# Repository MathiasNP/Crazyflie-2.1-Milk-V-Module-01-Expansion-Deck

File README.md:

# Crazyflie 2.1 Milk-V Duo Module 01 Expansion Deck
This project designs a PCB expansion deck for Bitcraze Crazyflie 2.1 including a dual-core GHz CPU with additional interfaces for communication

---
## CAD program
- **KiCad 9.0** 

## Key components
- **Milk-V Duo Module 01** 
- **SD card connector:** 32GB minimum
- **USB connector pads** 
- **Expansion connectors to Crazyflie** 
- **DC-DC converter for 3.3V**

### For testing
- **Crazyflie 2.1** with Crazyradio USB Dongle
- **Linux computer** 
	- With Docker installed
	- Preferably Linux Mint or Ubuntu
	- Minimum 4GB RAM, 8GB recommended
- **Jumper cables:** For Crazyflie-to-MilkV connection

### Desclaimer
SD/MMC flashing is not possible due to connection problems to the Duo Module. Surmised to be due to the usage of an EMI-Filter with too high series resistance
Recommended to either use the schematic design from the original EVB schematics and/or remove the EMI-Filter

---
## File Reference
- **`BT-MV Duo 01 Deck/`**: Project root folder.

- **`BT-MV Duo 01 Deck.kicad_pcb`**: KiCad PCB layout file.  
- **`BT-MV Duo 01 Deck.kicad_prl`**: KiCad project local settings file.  
- **`BT-MV Duo 01 Deck.kicad_pro`**: KiCad project file.  

- **`MV Duo 01 Deck Schematics/`**: Hierarchical schematics for the deck design.  
  - **`BT-MV Duo 01 Deck.kicad_sch`**: Top-level schematic.  
  - **`BT-Power_CFexp.kicad_sch`**: Power management and Crazyflie expansion interface.  
  - **`BT-SDcard.kicad_sch`**: microSD (SD/MMC) interface.  
  - **`BT-USB_UART.kicad_sch`**: USB interface and UART debug port.  
  - **`BT-CameraOV.kicad_sch`**: Camera connector and related signals.  
  - **`BT-MV_DM01.kicad_sch`**: Milk-V Duo Module 01 integration (pins, power, straps).  
  - **`BT-Others.kicad_sch`**: Miscellaneous signals and support circuits.  

- **`BT-MVD01 libraries/`**: Custom KiCad libraries used by the project.  
  - **`Symbols and Footprints/`**: Symbol/footprint library folder.  
  - **`3D Models/`**: 3D models for custom footprints.  

- **`BT-Milk V Duo S.pretty/`**: KiCad footprint library (`.pretty`).  
- **`BT-MV Duo 01 Deck.csv`**: BOM / component list.  
- **`BT-MV Duo 01 Deck.kicad_dru`**: KiCad custom design rules.  

- **`Related Work/`**: Reference material from related designs.  
  - **`CF Proto Exp/`**: Crazyflie expansion/deck project and documentation.  
  - **`Milk Module schematics/`**: Schematics of the Milk-V module and EVB.  
  - **`Camera OV5674/`**: Reference material for the OV5674 camera.

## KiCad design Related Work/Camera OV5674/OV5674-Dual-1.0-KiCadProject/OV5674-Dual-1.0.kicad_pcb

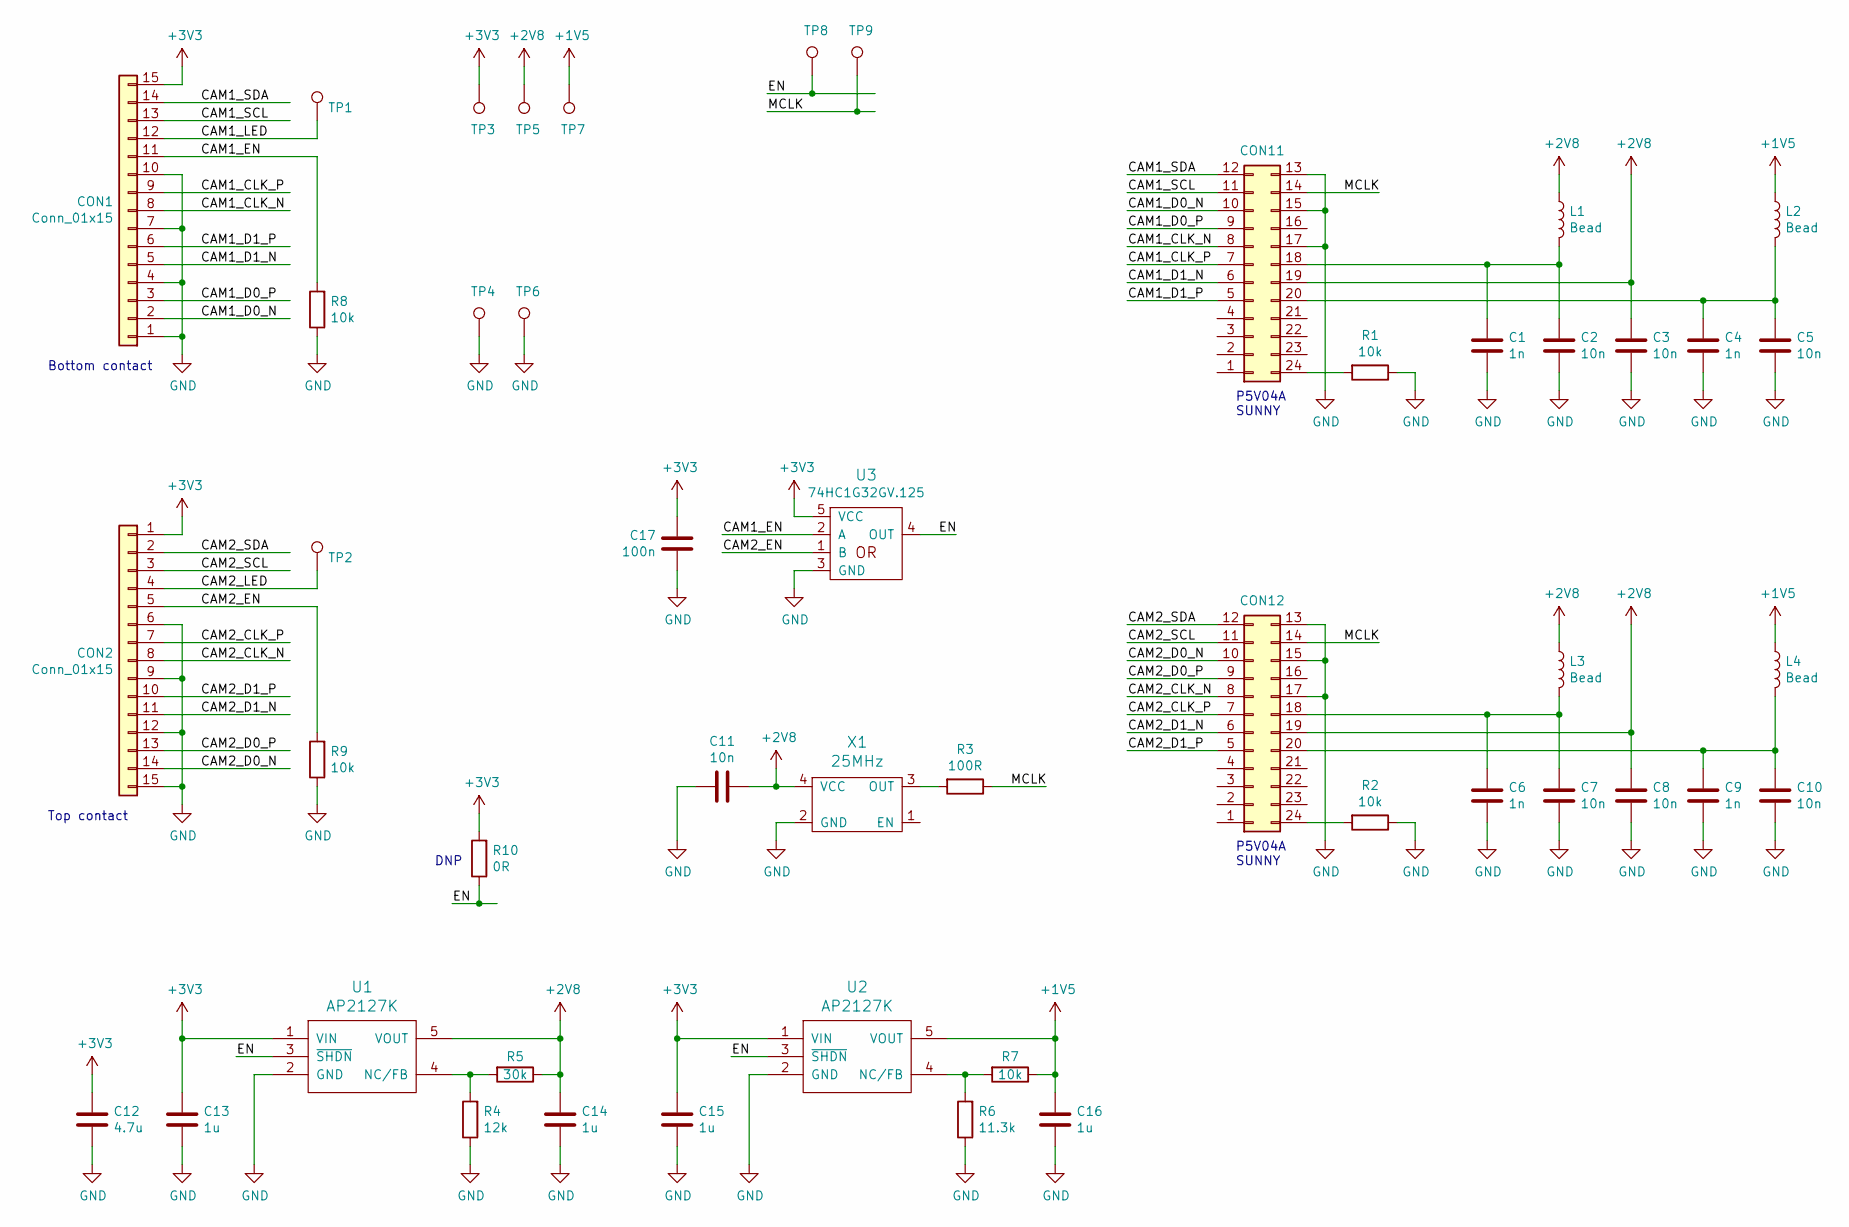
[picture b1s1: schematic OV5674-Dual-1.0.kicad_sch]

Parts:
C1, C4, C6, C9: 1n; C_0603_1608Metric
C2, C3, C5, C7, C8, C10, C11: 10n; C_0603_1608Metric
C12: 4.7u; C_0805_2012Metric
C13, C14, C15, C16: 1u; C_0603_1608Metric
C17: 100n; C_0603_1608Metric
CON1, CON2: Conn_01x15; TE_1-84952-5_1x15-1MP_P1.0mm_Horizontal
CON11, CON12: Conn_02x12_Counter_Clockwise; DF30FC-24DP-0.4V
L1, L2, L3, L4: Bead; L_0805_2012Metric
R1, R2, R7, R8, R9: 10k; R_0603_1608Metric
R3: 100R; R_0603_1608Metric
R4: 12k; R_0603_1608Metric
R5: 30k; R_0603_1608Metric
R6: 11.3k; R_0603_1608Metric
R10: 0R; R_0603_1608Metric
TP1, TP2, TP3, TP4: TestPoint; TestPoint_Pad_D1.5mm
TP5, TP6, TP7, TP8, TP9: TestPoint; TestPoint_Pad_D1.0mm
U1, U2: AP2127K; SOT-23-5
U3: 74xx1G32; SC-74A
X1: 25MHz; CFPS-39

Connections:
+1V5: C16.1, L2.1, L4.1, R7.1, TP7.1, U2.5 (VOUT)
+2V8: C3.1, C8.1, C11.1, C14.1, CON11.19, CON12.19, L1.1, L3.1, R5.1, TP5.1, U1.5 (VOUT), X1.4 (VCC)
+3V3: C12.1, C13.1, C15.1, C17.1, CON1.15, CON2.1, R10.2, TP3.1, U1.1 (VIN), U2.1 (VIN), U3.5 (VCC)
/CAM1_CLK_N: CON1.8, CON11.8
/CAM1_CLK_P: CON1.9, CON11.7
/CAM1_D0_N: CON1.2, CON11.10
/CAM1_D0_P: CON1.3, CON11.9
/CAM1_D1_N: CON1.5, CON11.6
/CAM1_D1_P: CON1.6, CON11.5
/CAM1_EN: CON1.11, R8.2, U3.2 (A)
/CAM1_LED: CON1.12, TP1.1
/CAM1_SCL: CON1.13, CON11.11
/CAM1_SDA: CON1.14, CON11.12
/CAM2_CLK_N: CON2.8, CON12.8
/CAM2_CLK_P: CON2.7, CON12.7
/CAM2_D0_N: CON2.14, CON12.10
/CAM2_D0_P: CON2.13, CON12.9
/CAM2_D1_N: CON2.11, CON12.6
/CAM2_D1_P: CON2.10, CON12.5
/CAM2_EN: CON2.5, R9.2, U3.1 (B)
/CAM2_LED: CON2.4, TP2.1
/CAM2_SCL: CON2.3, CON12.11
/CAM2_SDA: CON2.2, CON12.12
/EN: R10.1, TP8.1, U1.3 (~SHDN), U2.3 (~SHDN), U3.4 (OUT)
/MCLK: CON11.14, CON12.14, R3.1, TP9.1
GND: C1.2, C2.2, C3.2, C4.2, C5.2, C6.2, C7.2, C8.2, C9.2, C10.2, C11.2, C12.2, C13.2, C14.2, C15.2, C16.2, C17.2, CON1.1, CON1.4, CON1.7, CON1.10, CON2.6, CON2.9, CON2.12, CON2.15, CON11.13, CON11.15, CON11.17, CON12.13, CON12.15, CON12.17, R1.1, R2.1, R4.1, R6.1, R8.1, R9.1, TP4.1, TP6.1, U1.2 (GND), U2.2 (GND), U3.3 (GND), X1.2 (GND)
unnamed: C1.1, C2.1, CON11.18, L1.2
unnamed: C4.1, C5.1, CON11.20, L2.2
unnamed: C6.1, C7.1, CON12.18, L3.2
unnamed: C9.1, C10.1, CON12.20, L4.2
unnamed: CON11.24, R1.2
unnamed: CON12.24, R2.2
unnamed: R3.2, X1.3 (OUT)
unnamed: R4.2, R5.2, U1.4 (NC/FB)
unnamed: R6.2, R7.2, U2.4 (NC/FB)

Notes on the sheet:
Bottom contact
DNP
P5V04A SUNNY
Top contact

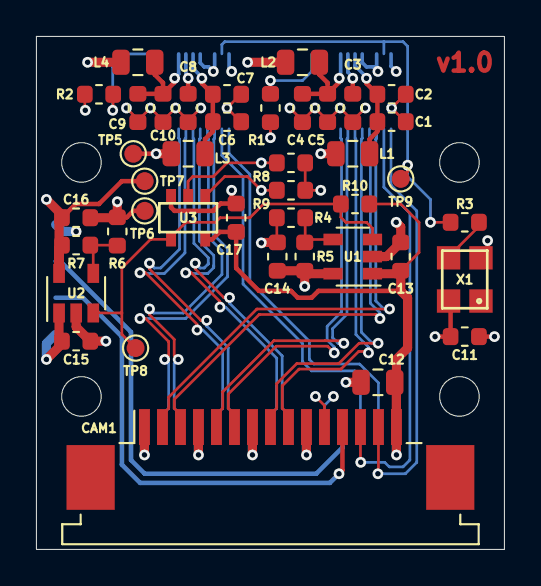
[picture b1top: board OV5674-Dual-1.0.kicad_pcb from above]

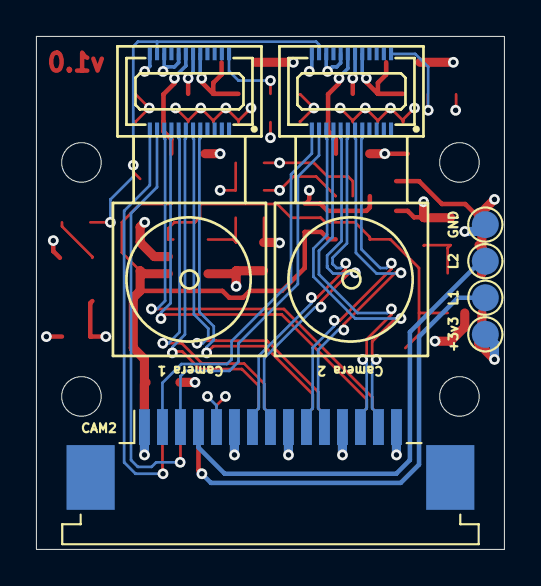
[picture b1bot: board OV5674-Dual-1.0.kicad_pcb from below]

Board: 4 copper layers, 26.0 x 28.5 mm, 48 parts (7 on the bottom side), 35 nets.

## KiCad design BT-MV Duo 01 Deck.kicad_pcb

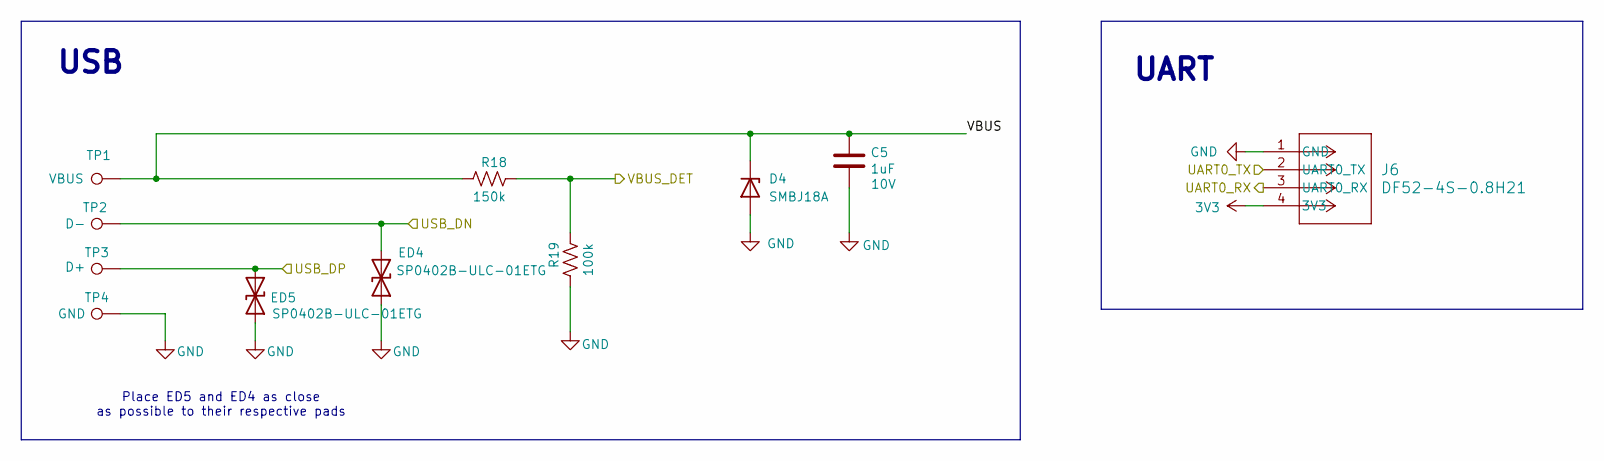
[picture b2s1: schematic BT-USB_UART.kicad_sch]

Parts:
C5: 1uF; C_0603_1608Metric
D4: SMBJ18A; D_SOD-123F
ED4, ED5: SP0402B-ULC-01ETG; D_0402_1005Metric
J6: DF52-4S-0.8H21; CONN4X1_DF52-4S-0.8H21_HIR
R18: 150k; R_0201_0603Metric_Pad0.64x0.40mm_HandSolder
R19: 100k; R_0201_0603Metric_Pad0.64x0.40mm_HandSolder
TP1: VBUS; TestPoint_Pad_D1.0mm
TP2: D-; TestPoint_Pad_D1.0mm
TP3: D+; TestPoint_Pad_D1.0mm
TP4: GND; TestPoint_Pad_D1.0mm

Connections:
3V3: J6.4 (3V3); also elsewhere on the board
/CF Proto EXP/VBUS: C5.1, D4.1 (K), R18.2, TP1.1; also elsewhere on the board
/Milk Module/UART0_RX: J6.3 (UART0_RX); also elsewhere on the board
/Milk Module/UART0_TX: J6.2 (UART0_TX); also elsewhere on the board
/Milk Module/USB_DN: ED4.2 (A2), TP2.1; also elsewhere on the board
/Milk Module/USB_DP: ED5.2 (A2), TP3.1; also elsewhere on the board
/Milk Module/VBUS_DET: R18.1, R19.1; also elsewhere on the board
GND: C5.2, D4.2 (A), ED4.1 (A1), ED5.1 (A1), J6.1 (GND), R19.2, TP4.1; also elsewhere on the board

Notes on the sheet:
UART
USB
Place ED5 and ED4 as close as possible to their respective pads

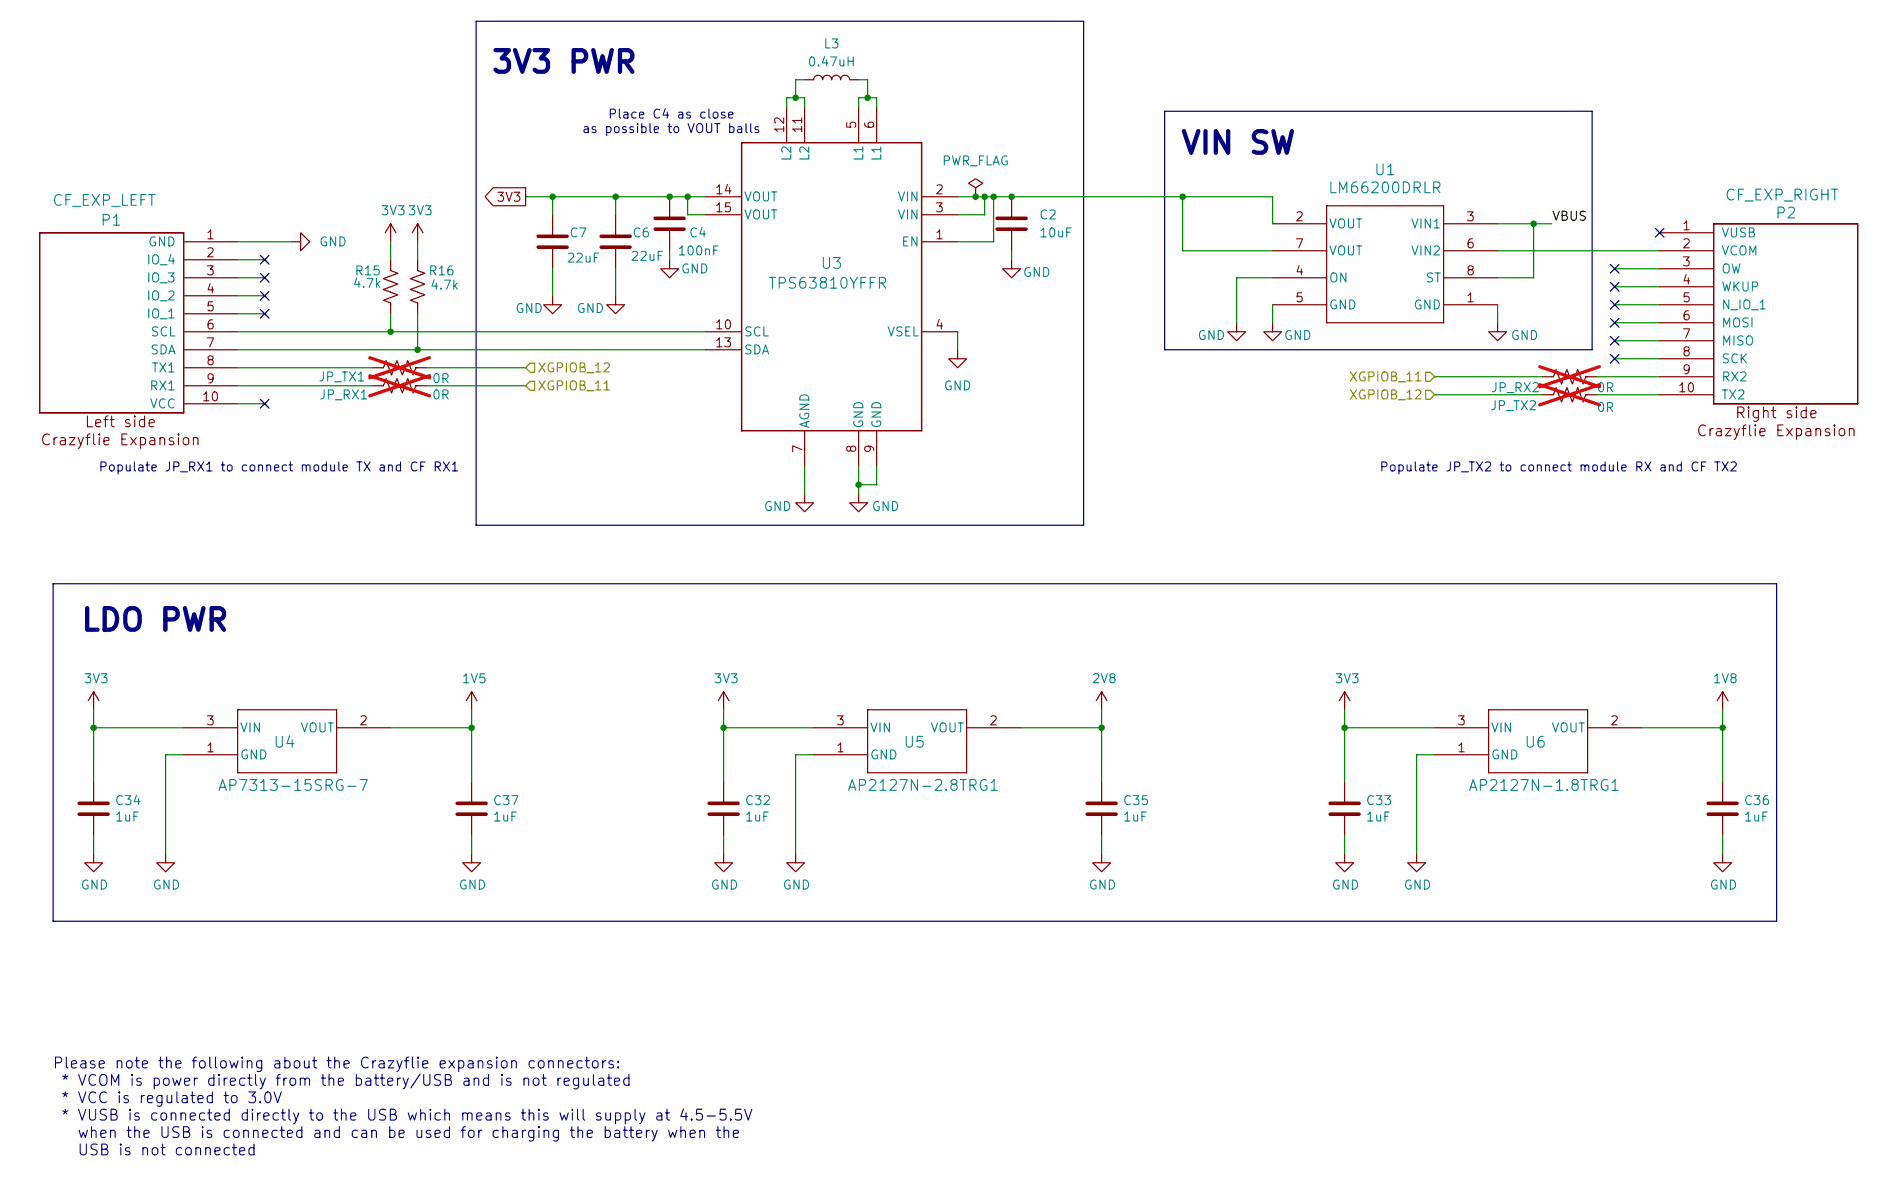
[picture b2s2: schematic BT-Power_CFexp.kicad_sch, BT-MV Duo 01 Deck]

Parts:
C2: 10uF; C_0201_0603Metric_Pad0.64x0.40mm_HandSolder
C4: 100nF; C_0201_0603Metric_Pad0.64x0.40mm_HandSolder
C6, C7: 22uF; C_0402_1005Metric_Pad0.74x0.62mm_HandSolder
C32, C33, C34, C35, C36, C37: 1uF; C_0603_1608Metric
JP_RX1, JP_RX2: 0R; R_0402_1005Metric; not fitted
JP_TX1, JP_TX2: 0R; R_0402_1005Metric; not fitted
L3: 0.47uH; L_0201_0603Metric_Pad0.64x0.40mm_HandSolder
P1: CF_EXP_LEFT; CF2-DECK-SMD-HOLES
P2: CF_EXP_RIGHT; CF2-DECK-SMD-HOLES
R15, R16: 4.7k; R_0201_0603Metric_Pad0.64x0.40mm_HandSolder
U1: LM66200DRLR; SOT-5X3_DRL_TEX
U3: TPS63810YFFR; YFF0015AHAN
U4: AP7313-15SRG-7; SOT-23_DIO
U5: AP2127N-2.8TRG1; SOT-23_DIO
U6: AP2127N-1.8TRG1; SOT-23_DIO

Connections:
1V5: C37.1, U4.2 (VOUT); also elsewhere on the board
1V8: C36.1, U6.2 (VOUT); also elsewhere on the board
2V8: C35.1, U5.2 (VOUT); also elsewhere on the board
3V3: C4.1, C6.1, C7.1, C32.1, C33.1, C34.1, R15.2, R16.2, U3.14 (VOUT), U3.15 (VOUT), U4.3 (VIN), U5.3 (VIN), U6.3 (VIN); also elsewhere on the board
/CF Proto EXP/VBUS: U1.3 (VIN1), U1.8 (ST); also elsewhere on the board
/Milk Module/XGPIOB_11: JP_RX1.2, JP_RX2.1; also elsewhere on the board
/Milk Module/XGPIOB_12: JP_TX1.2, JP_TX2.1; also elsewhere on the board
GND: C2.2, C4.2, C6.2, C7.2, C32.2, C33.2, C34.2, C35.2, C36.2, C37.2, P1.1 (GND), U1.1 (GND), U1.4 (ON), U1.5 (GND), U3.4 (VSEL), U3.7 (AGND), U3.8 (GND), U3.9 (GND), U4.1 (GND), U5.1 (GND), U6.1 (GND); also elsewhere on the board
unnamed: L3.1, U3.5 (L1), U3.6 (L1)
unnamed: L3.2, U3.11 (L2), U3.12 (L2)
unnamed: JP_RX1.1, P1.9 (RX1)
unnamed: P1.6 (SCL), R15.1, U3.10 (SCL)
unnamed: P1.7 (SDA), R16.1, U3.13 (SDA)
unnamed: JP_TX1.1, P1.8 (TX1)
unnamed: JP_RX2.2, P2.9 (RX2)
unnamed: JP_TX2.2, P2.10 (TX2)
unnamed: P2.2 (VCOM), U1.6 (VIN2)
unnamed: C2.1, U1.2 (VOUT), U1.7 (VOUT), U3.1 (EN), U3.2 (VIN), U3.3 (VIN)

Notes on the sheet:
Populate JP_TX2 to connect module RX and CF TX2
Please note the following about the Crazyflie expansion connectors: * VCOM is power directly from the battery/USB and is not regulated * VCC is regulated to 3.0V * VUSB is connected directly to the USB which means this will supply at 4.5-5.5V when the USB is connected and can be used for charging t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
LDO PWR
3V3 PWR
Populate JP_RX1 to connect module TX and CF RX1
VIN SW
Place C4 as close as possible to VOUT balls

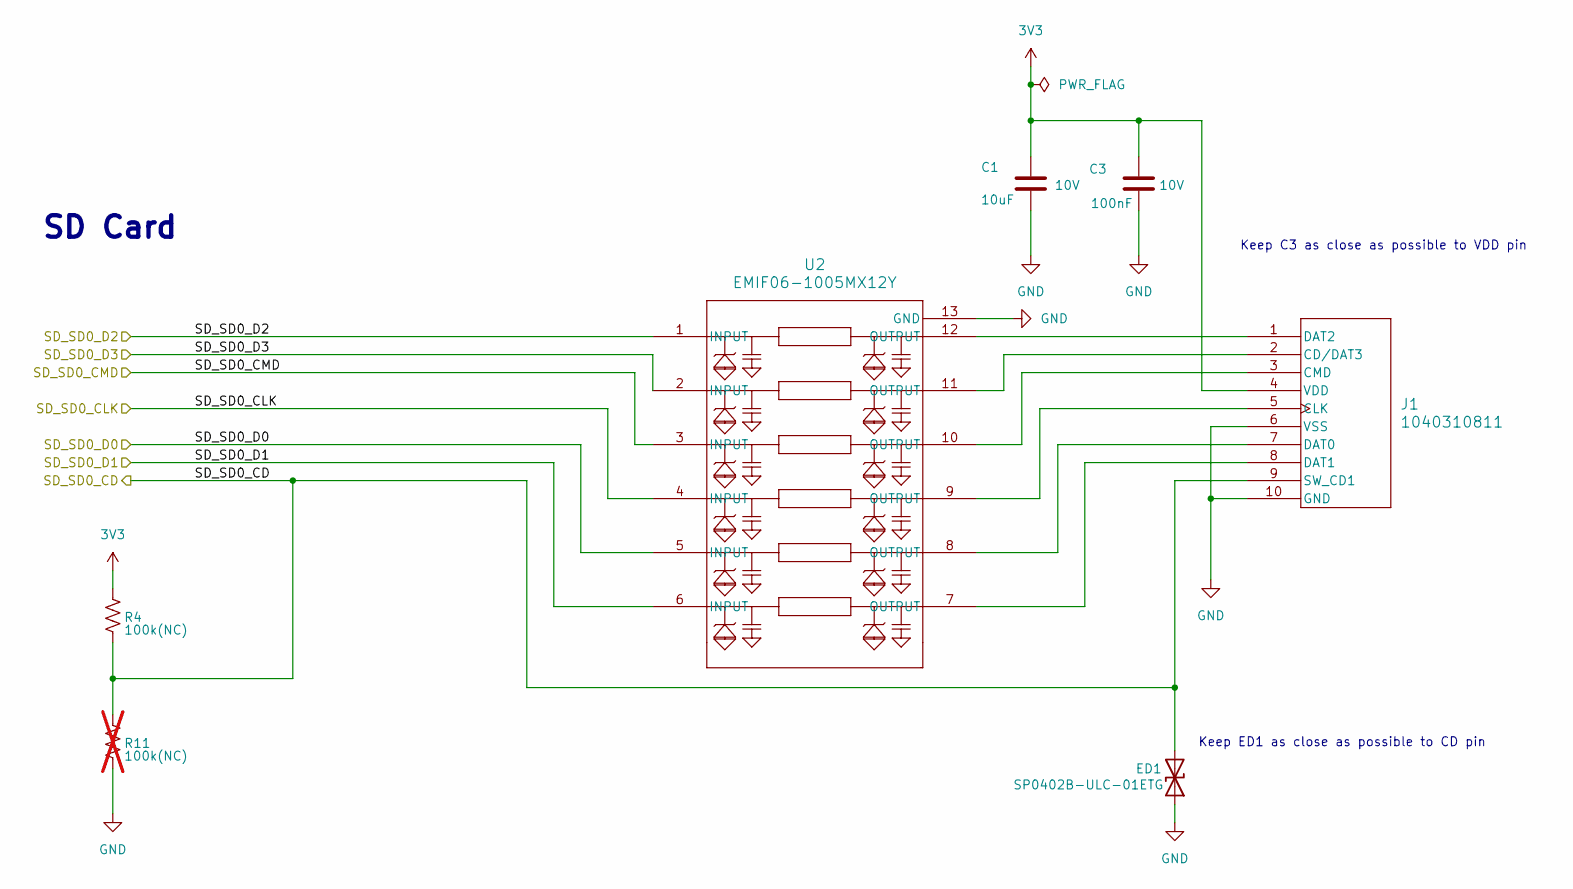
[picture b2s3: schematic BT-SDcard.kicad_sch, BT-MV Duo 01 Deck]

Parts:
C1: 10uF; C_0603_1608Metric_Pad1.08x0.95mm_HandSolder; VOLTAGE 10V; TOLERANCE 10%
C3: 100nF; C_0402_1005Metric_Pad0.74x0.62mm_HandSolder; VOLTAGE 10V; TOLERANCE 10%
ED1: SP0402B-ULC-01ETG; D_0402_1005Metric
J1: 1040310811; 104031-0811_MOL
R4: 100k(NC); R_0402_1005Metric_Pad0.72x0.64mm_HandSolder
R11: 100k(NC); R_0402_1005Metric_Pad0.72x0.64mm_HandSolder; not fitted
U2: EMIF06-1005MX12Y; SON_5MX12Y_STM

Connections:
3V3: C1.1, C3.1, J1.4 (VDD), R4.1; also elsewhere on the board
/Milk Module/SD_SD0_CD: ED1.2 (A2), J1.9 (SW_CD1), R4.2, R11.1; also elsewhere on the board
/Milk Module/SD_SD0_CLK: U2.4 (INPUT); also elsewhere on the board
/Milk Module/SD_SD0_CMD: U2.3 (INPUT); also elsewhere on the board
/Milk Module/SD_SD0_D0: U2.5 (INPUT); also elsewhere on the board
/Milk Module/SD_SD0_D1: U2.6 (INPUT); also elsewhere on the board
/Milk Module/SD_SD0_D2: U2.1 (INPUT); also elsewhere on the board
/Milk Module/SD_SD0_D3: U2.2 (INPUT); also elsewhere on the board
GND: C1.2, C3.2, ED1.1 (A1), J1.6 (VSS), J1.10 (GND), R11.2, U2.13 (GND); also elsewhere on the board
unnamed: J1.2 (CD/DAT3), U2.11 (OUTPUT)
unnamed: J1.5 (CLK), U2.9 (OUTPUT)
unnamed: J1.3 (CMD), U2.10 (OUTPUT)
unnamed: J1.7 (DAT0), U2.8 (OUTPUT)
unnamed: J1.8 (DAT1), U2.7 (OUTPUT)
unnamed: J1.1 (DAT2), U2.12 (OUTPUT)

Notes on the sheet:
Keep ED1 as close as possible to CD pin
SD Card
Keep C3 as close as possible to VDD pin

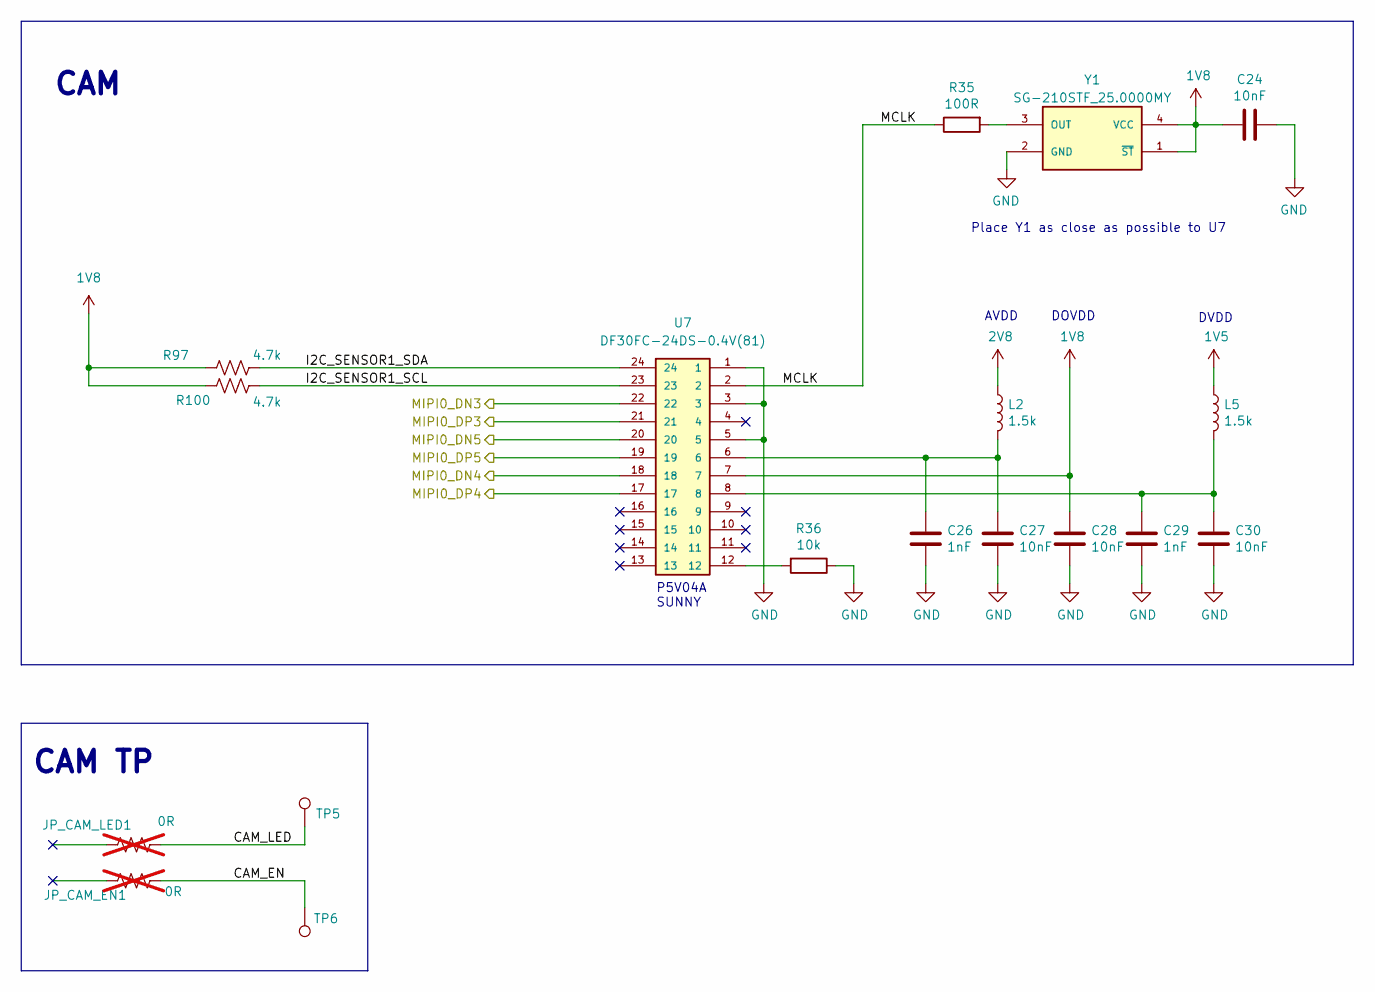
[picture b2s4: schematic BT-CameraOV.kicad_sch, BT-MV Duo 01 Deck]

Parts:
C24, C27, C28, C30: 10nF; C_0603_1608Metric
C26, C29: 1nF; C_0603_1608Metric
JP_CAM_EN1: 0R; R_0402_1005Metric; not fitted
JP_CAM_LED1: 0R; R_0402_1005Metric; not fitted
L2, L5: 1.5k; L_0805_2012Metric
R35: 100R; R_0603_1608Metric
R36: 10k; R_0603_1608Metric
R97, R100: 4.7k; R_0201_0603Metric_Pad0.64x0.40mm_HandSolder
TP5, TP6: TestPoint; TestPoint_Pad_D1.0mm
U7: DF30FC-24DS-0.4V(81); DF30FC-24DS
Y1: SG-210STF_25.0000MY; OSCCC250X200X90

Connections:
1V5: L5.1; also elsewhere on the board
1V8: C24.1, C28.1, R97.1, R100.1, U7.7, Y1.1 (~ST), Y1.4 (VCC); also elsewhere on the board
2V8: L2.1; also elsewhere on the board
/Camera OV/CAM_EN: JP_CAM_EN1.2, TP6.1
/Camera OV/CAM_LED: JP_CAM_LED1.2, TP5.1
/Camera OV/I2C_SENSOR1_SCL: R100.2, U7.23
/Camera OV/I2C_SENSOR1_SDA: R97.2, U7.24
/Camera OV/MCLK: R35.1, U7.2
/Milk Module/MIPI0_DN3: U7.22; also elsewhere on the board
/Milk Module/MIPI0_DN4: U7.18; also elsewhere on the board
/Milk Module/MIPI0_DN5: U7.20; also elsewhere on the board
/Milk Module/MIPI0_DP3: U7.21; also elsewhere on the board
/Milk Module/MIPI0_DP4: U7.17; also elsewhere on the board
/Milk Module/MIPI0_DP5: U7.19; also elsewhere on the board
GND: C24.2, C26.2, C27.2, C28.2, C29.2, C30.2, R36.1, U7.1, U7.3, U7.5, Y1.2 (GND); also elsewhere on the board
unnamed: C26.1, C27.1, L2.2, U7.6
unnamed: C29.1, C30.1, L5.2, U7.8
unnamed: R36.2, U7.12
unnamed: R35.2, Y1.3 (OUT)

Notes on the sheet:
DOVDD
CAM TP
DVDD
Place Y1 as close as possible to U7
CAM
P5V04A SUNNY
AVDD

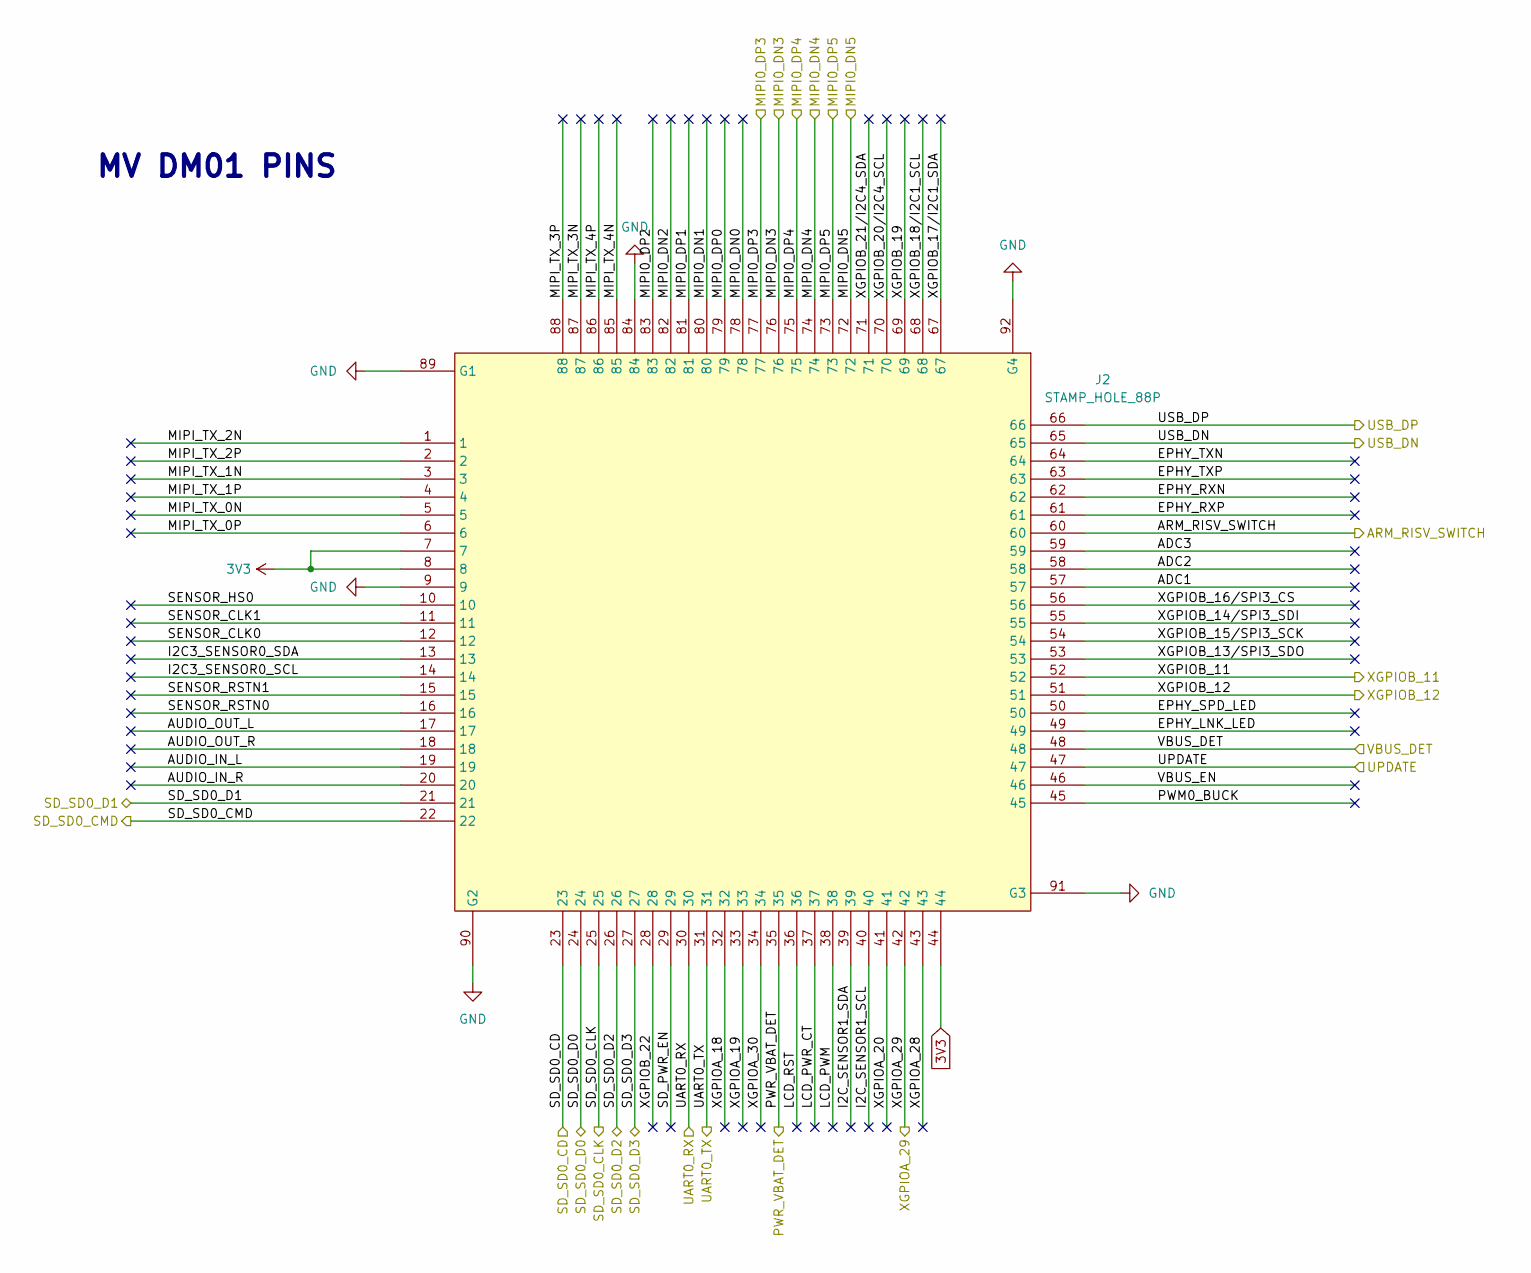
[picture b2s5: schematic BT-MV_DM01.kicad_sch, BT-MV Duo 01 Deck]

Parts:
J2: STAMP_HOLE_88P; MilkV_Duo_Module

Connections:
3V3: J2.7, J2.8, J2.44; also elsewhere on the board
/Milk Module/ADC1: J2.57
/Milk Module/ADC2: J2.58
/Milk Module/ADC3: J2.59
/Milk Module/ARM_RISV_SWITCH: J2.60; also elsewhere on the board
/Milk Module/AUDIO_IN_L: J2.19
/Milk Module/AUDIO_IN_R: J2.20
/Milk Module/AUDIO_OUT_L: J2.17
/Milk Module/AUDIO_OUT_R: J2.18
/Milk Module/EPHY_LNK_LED: J2.49
/Milk Module/EPHY_RXN: J2.62
/Milk Module/EPHY_RXP: J2.61
/Milk Module/EPHY_SPD_LED: J2.50
/Milk Module/EPHY_TXN: J2.64
/Milk Module/EPHY_TXP: J2.63
/Milk Module/I2C3_SENSOR0_SCL: J2.14
/Milk Module/I2C3_SENSOR0_SDA: J2.13
/Milk Module/I2C_SENSOR1_SCL: J2.40
/Milk Module/I2C_SENSOR1_SDA: J2.39
/Milk Module/LCD_PWM: J2.38
/Milk Module/LCD_PWR_CT: J2.37
/Milk Module/LCD_RST: J2.36
/Milk Module/MIPI0_DN0: J2.78
/Milk Module/MIPI0_DN1: J2.80
/Milk Module/MIPI0_DN2: J2.82
/Milk Module/MIPI0_DN3: J2.76; also elsewhere on the board
/Milk Module/MIPI0_DN4: J2.74; also elsewhere on the board
/Milk Module/MIPI0_DN5: J2.72; also elsewhere on the board
/Milk Module/MIPI0_DP0: J2.79
/Milk Module/MIPI0_DP1: J2.81
/Milk Module/MIPI0_DP2: J2.83
/Milk Module/MIPI0_DP3: J2.77; also elsewhere on the board
/Milk Module/MIPI0_DP4: J2.75; also elsewhere on the board
/Milk Module/MIPI0_DP5: J2.73; also elsewhere on the board
/Milk Module/MIPI_TX_0N: J2.5
/Milk Module/MIPI_TX_0P: J2.6
/Milk Module/MIPI_TX_1N: J2.3
/Milk Module/MIPI_TX_1P: J2.4
/Milk Module/MIPI_TX_2N: J2.1
/Milk Module/MIPI_TX_2P: J2.2
/Milk Module/MIPI_TX_3N: J2.87
/Milk Module/MIPI_TX_3P: J2.88
/Milk Module/MIPI_TX_4N: J2.85
/Milk Module/MIPI_TX_4P: J2.86
/Milk Module/PWM0_BUCK: J2.45
/Milk Module/PWR_VBAT_DET: J2.35; also elsewhere on the board
/Milk Module/SD_PWR_EN: J2.29
/Milk Module/SD_SD0_CD: J2.23; also elsewhere on the board
/Milk Module/SD_SD0_CLK: J2.25; also elsewhere on the board
/Milk Module/SD_SD0_CMD: J2.22; also elsewhere on the board
/Milk Module/SD_SD0_D0: J2.24; also elsewhere on the board
/Milk Module/SD_SD0_D1: J2.21; also elsewhere on the board
/Milk Module/SD_SD0_D2: J2.26; also elsewhere on the board
/Milk Module/SD_SD0_D3: J2.27; also elsewhere on the board
/Milk Module/SENSOR_CLK0: J2.12
/Milk Module/SENSOR_CLK1: J2.11
/Milk Module/SENSOR_HS0: J2.10
/Milk Module/SENSOR_RSTN0: J2.16
/Milk Module/SENSOR_RSTN1: J2.15
/Milk Module/UART0_RX: J2.30; also elsewhere on the board
/Milk Module/UART0_TX: J2.31; also elsewhere on the board
/Milk Module/UPDATE: J2.47; also elsewhere on the board
/Milk Module/USB_DN: J2.65; also elsewhere on the board
/Milk Module/USB_DP: J2.66; also elsewhere on the board
/Milk Module/VBUS_DET: J2.48; also elsewhere on the board
/Milk Module/VBUS_EN: J2.46
/Milk Module/XGPIOA_18: J2.32
/Milk Module/XGPIOA_19: J2.33
/Milk Module/XGPIOA_20: J2.41
/Milk Module/XGPIOA_28: J2.43
/Milk Module/XGPIOA_29: J2.42; also elsewhere on the board
/Milk Module/XGPIOA_30: J2.34
/Milk Module/XGPIOB_11: J2.52; also elsewhere on the board
/Milk Module/XGPIOB_12: J2.51; also elsewhere on the board
/Milk Module/XGPIOB_13/SPI3_SDO: J2.53
/Milk Module/XGPIOB_14/SPI3_SDI: J2.55
/Milk Module/XGPIOB_15/SPI3_SCK: J2.54
/Milk Module/XGPIOB_16/SPI3_CS: J2.56
/Milk Module/XGPIOB_17/I2C1_SDA: J2.67
/Milk Module/XGPIOB_18/I2C1_SCL: J2.68
/Milk Module/XGPIOB_19: J2.69
/Milk Module/XGPIOB_20/I2C4_SCL: J2.70
/Milk Module/XGPIOB_21/I2C4_SDA: J2.71
/Milk Module/XGPIOB_22: J2.28
GND: J2.9, J2.84, J2.89 (G1), J2.90 (G2), J2.91 (G3), J2.92 (G4); also elsewhere on the board

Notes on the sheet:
MV DM01 PINS

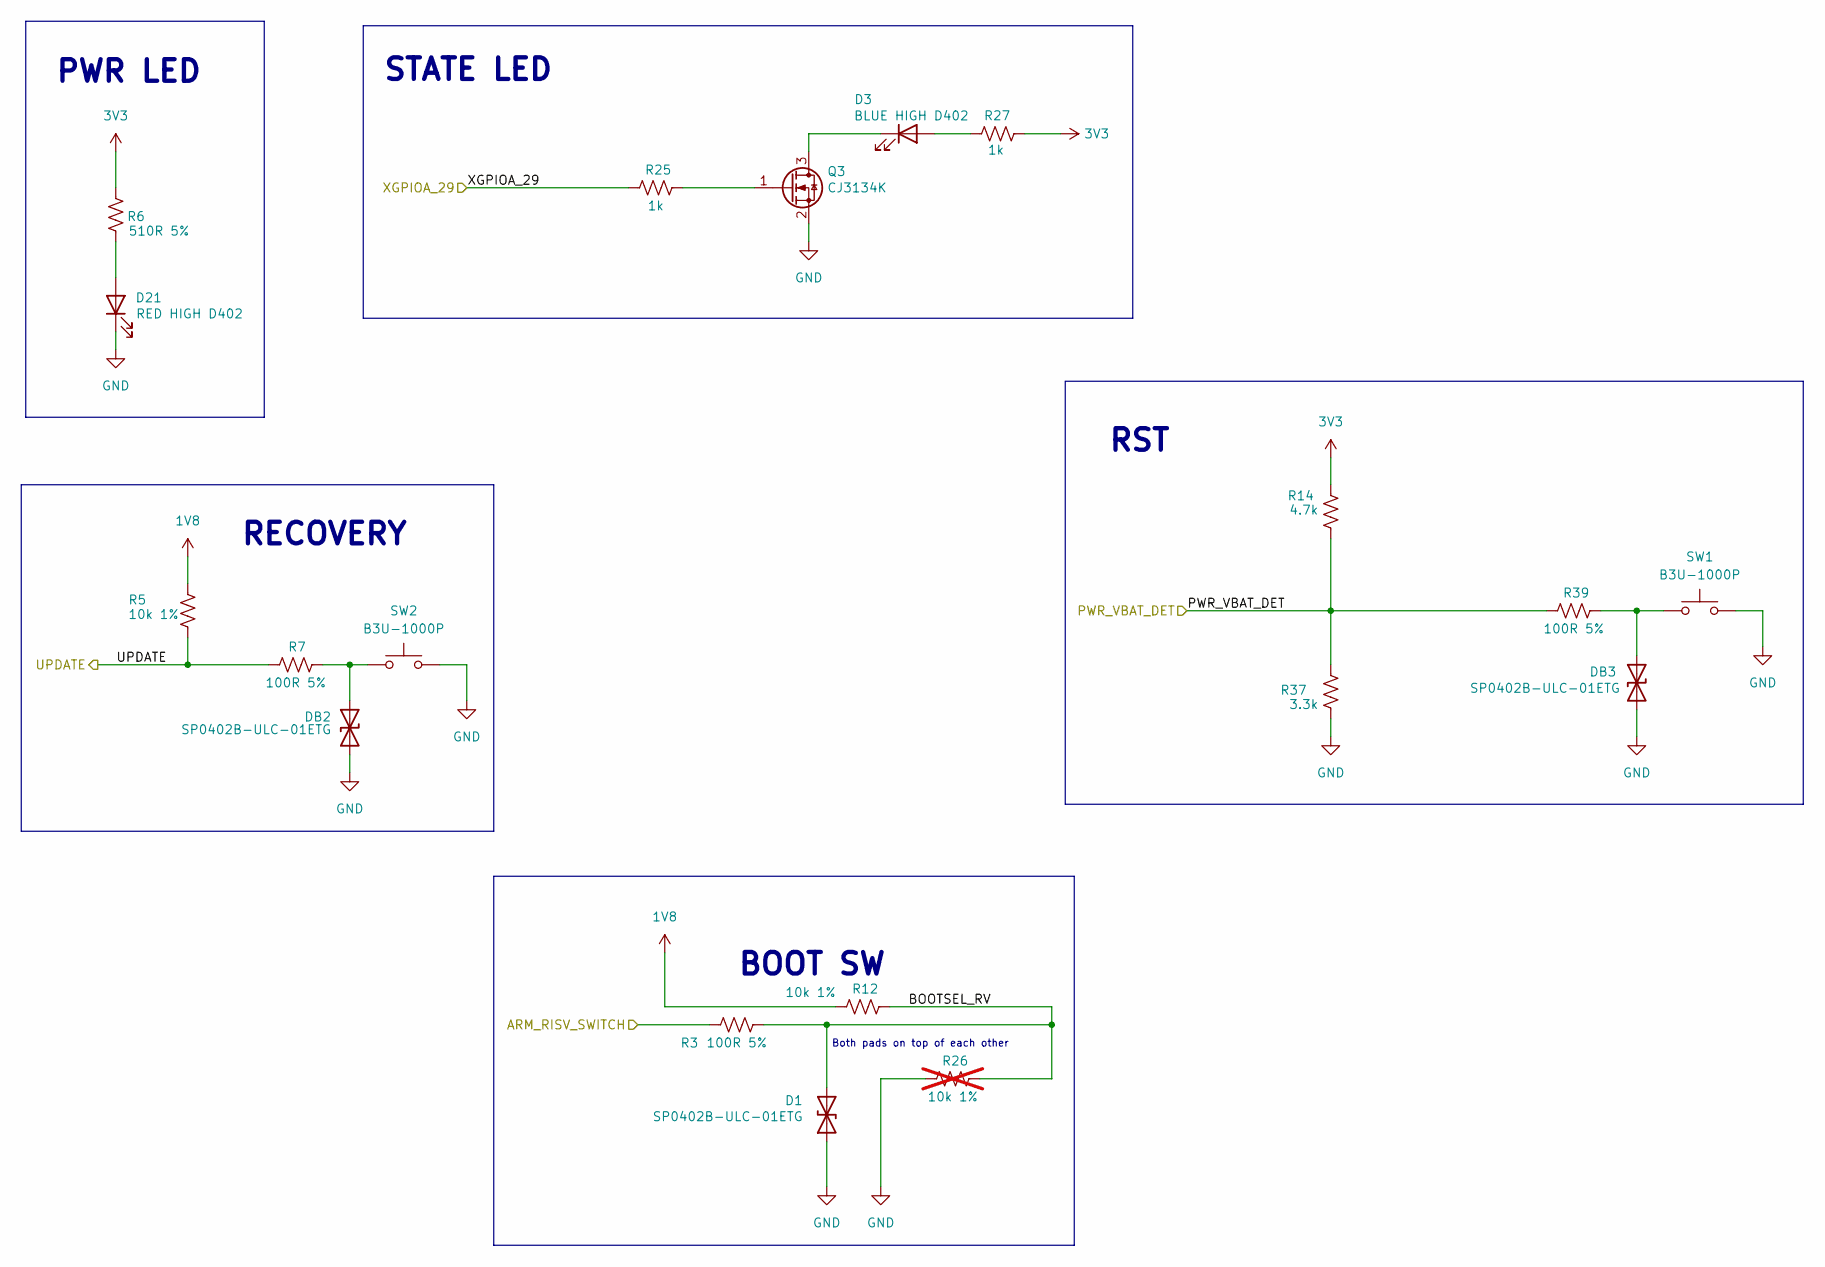
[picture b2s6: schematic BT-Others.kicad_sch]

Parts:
D1: SP0402B-ULC-01ETG; D_0402_1005Metric
D3: BLUE HIGH D402; LED_0402_1005Metric_Pad0.77x0.64mm_HandSolder
D21: RED HIGH D402; LED_0402_1005Metric_Pad0.77x0.64mm_HandSolder
DB2, DB3: SP0402B-ULC-01ETG; D_0402_1005Metric
Q3: CJ3134K; SOT-723
R3, R7, R39: 100R 5%; R_0201_0603Metric_Pad0.64x0.40mm_HandSolder
R5, R12: 10k 1%; R_0201_0603Metric_Pad0.64x0.40mm_HandSolder
R6: 510R 5%; R_0402_1005Metric_Pad0.72x0.64mm_HandSolder
R14: 4.7k; R_0201_0603Metric_Pad0.64x0.40mm_HandSolder
R25, R27: 1k; R_0402_1005Metric_Pad0.72x0.64mm_HandSolder
R26: 10k 1%; R_0201_0603Metric_Pad0.64x0.40mm_HandSolder; not fitted
R37: 3.3k; R_0201_0603Metric_Pad0.64x0.40mm_HandSolder
SW1, SW2: B3U-1000P; SW_SPST_B3U-1000P

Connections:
1V8: R5.1, R12.1; also elsewhere on the board
3V3: R6.1, R14.2, R27.1; also elsewhere on the board
/Milk Module/ARM_RISV_SWITCH: R3.1; also elsewhere on the board
/Milk Module/PWR_VBAT_DET: R14.1, R37.2, R39.1; also elsewhere on the board
/Milk Module/UPDATE: R5.2, R7.1; also elsewhere on the board
/Milk Module/XGPIOA_29: R25.1; also elsewhere on the board
/SD Card/BOOTSEL_RV: D1.2 (A2), R3.2, R12.2, R26.2
GND: D1.1 (A1), D21.1 (K), DB2.2 (A2), DB3.2 (A2), Q3.2 (S), R26.1, R37.1, SW1.2, SW2.2; also elsewhere on the board
unnamed: D3.2 (A), R27.2
unnamed: D3.1 (K), Q3.3 (D)
unnamed: D21.2 (A), R6.2
unnamed: DB2.1 (A1), R7.2, SW2.1
unnamed: DB3.1 (A1), R39.2, SW1.1
unnamed: Q3.1 (G), R25.2

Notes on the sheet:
RST
BOOT SW
Both pads on top of each other
STATE LED
RECOVERY
PWR LED
